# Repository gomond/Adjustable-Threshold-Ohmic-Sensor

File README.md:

# Adjustable Threshold Ohmic Sensor
 Adjustable Threshold Ohmic Sensor designed to operate with current Masso CNC Plasma
 I have added an enable override jumper so that ti will function with the current G200
 command and anticipate that, Masso in their wisdom will ad a configurable enable output pin function to
 the G200 in an upcomming release as this makes the device much safer again by allowing full gapped isolation 
 on top of the optical isolation. 
 I have also added a fuse to the design, that is up to the end user to decide on or just place a link.
 
 I have tested it on my machine and it works adequatly there is possibly a lot of room for improvement 
 and as such is public dommain so feel free to fork and alter it as you please.
 All parts for the prototype including the din mount enclosure are available from RS components.

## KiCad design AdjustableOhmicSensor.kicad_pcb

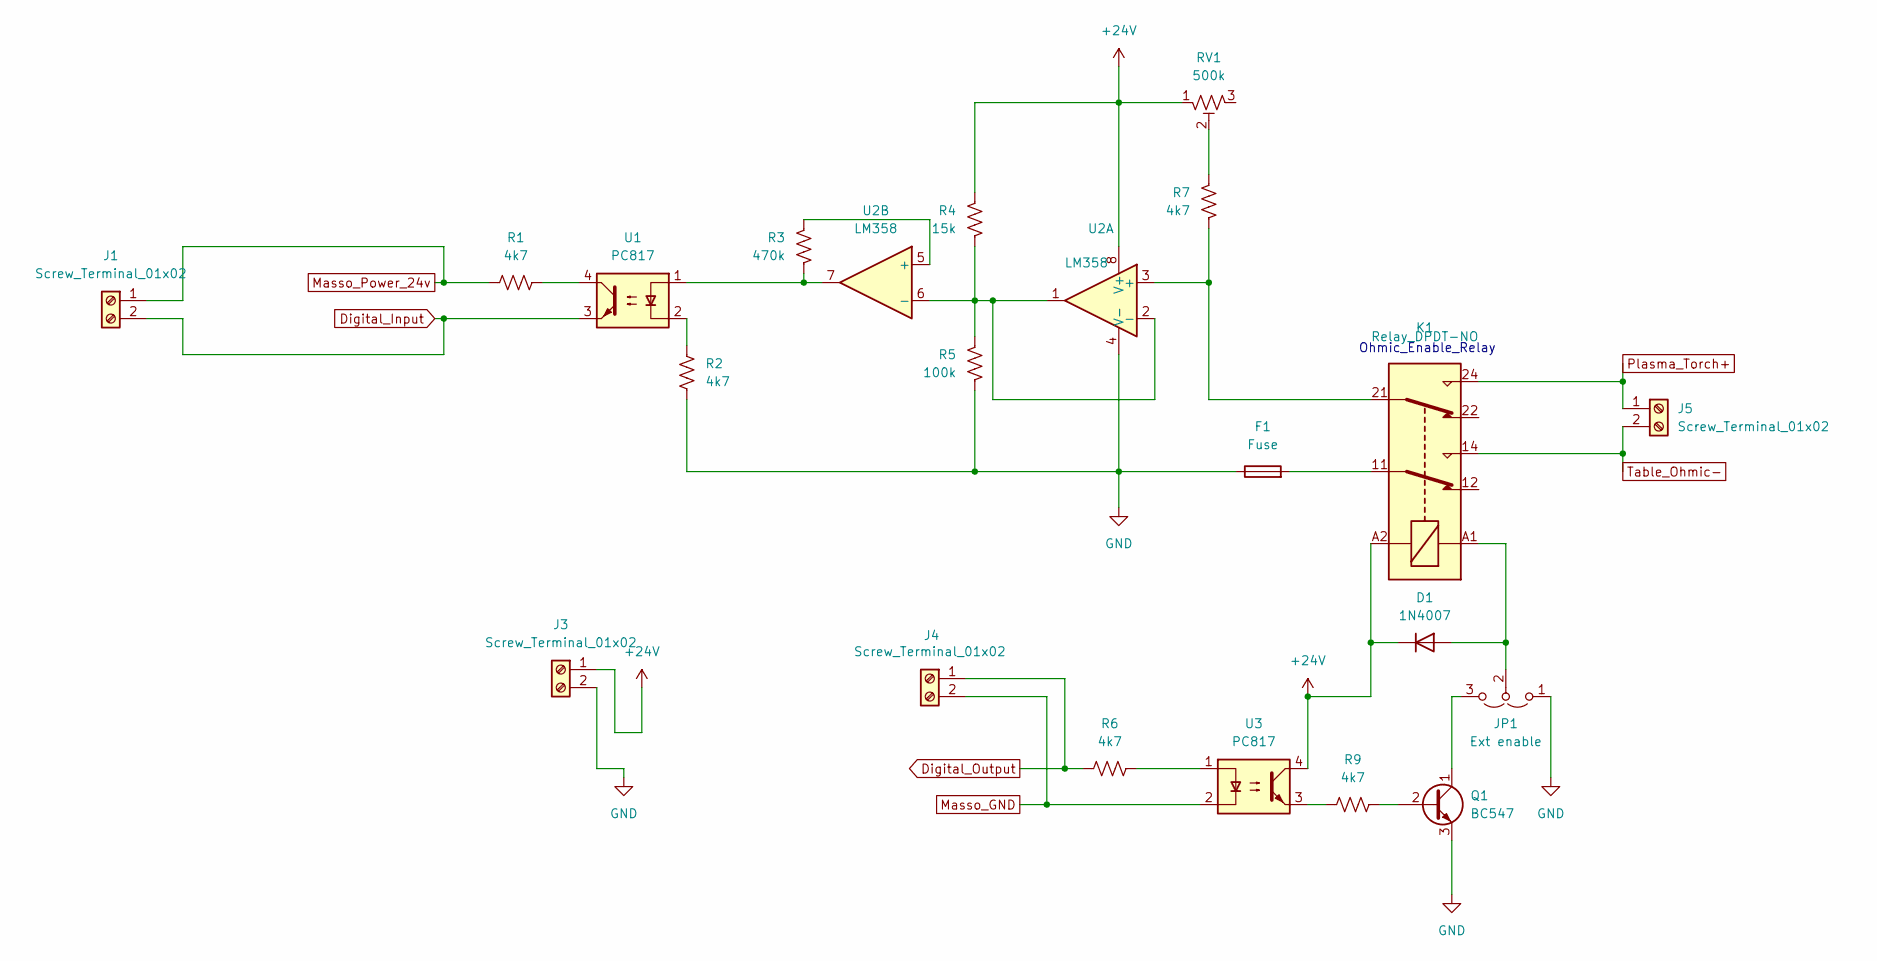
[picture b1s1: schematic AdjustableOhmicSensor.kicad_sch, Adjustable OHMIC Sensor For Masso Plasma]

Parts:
D1: 1N4007; D_DO-41_SOD81_P10.16mm_Horizontal
F1: Fuse; R_Axial_DIN0207_L6.3mm_D2.5mm_P10.16mm_Horizontal
J1, J3, J4: Screw_Terminal_01x02; TerminalBlock_bornier-2_P5.08mm
J5: Screw_Terminal_01x02; TerminalBlock_MetzConnect_Type171_RT13702HBWC_1x02_P7.50mm_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
JP1: Ext enable; PinHeader_1x03_P2.54mm_Vertical
K1: Relay_DPDT-NO; Relay_DPDT_Schrack-RT2-FormC-Dual-Coil_RM5mm
Q1: BC547; TO-92_Inline
R1, R2, R6, R7, R9: 4k7; R_Axial_DIN0207_L6.3mm_D2.5mm_P10.16mm_Horizontal
R3: 470k; R_Axial_DIN0207_L6.3mm_D2.5mm_P10.16mm_Horizontal
R4: 15k; R_Axial_DIN0207_L6.3mm_D2.5mm_P10.16mm_Horizontal
R5: 100k; R_Axial_DIN0207_L6.3mm_D2.5mm_P10.16mm_Horizontal
RV1: 500k; Potentiometer_Bourns_3296W_Vertical
U1, U3: PC817; DIP-4_W7.62mm
U2: LM358; DIP-8_W7.62mm

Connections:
+24V: D1.1 (K), J3.1, K1.A2, R4.1, RV1.1, U2.8 (V+), U3.4
Digital_Input: J1.2, U1.3
Digital_Output: J4.1, R6.1
GND: F1.1, J3.2, JP1.1 (A), Q1.3 (E), R2.1, R5.2, U2.4 (V-)
Masso_GND: J4.2, U3.2
Masso_Power_24v: J1.1, R1.1
unnamed: D1.2 (A), JP1.2 (C), K1.A1
unnamed: F1.2, K1.11
unnamed: JP1.3 (B), Q1.1 (C)
unnamed: Q1.2 (B), R9.2
unnamed: R1.2, U1.4
unnamed: R2.2, U1.2
unnamed: R3.2, U1.1, U2.7
unnamed: R6.2, U3.1
unnamed: R7.1, RV1.2
unnamed: R9.1, U3.3
unnamed: K1.21, R7.2, U2.3 (+)
unnamed: R4.2, R5.1, U2.1, U2.2 (-), U2.6 (-)
unnamed: R3.1, U2.5 (+)
Plasma_Torch+: J5.1, K1.24
Table_Ohmic-: J5.2, K1.14

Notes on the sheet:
Ohmic_Enable_Relay

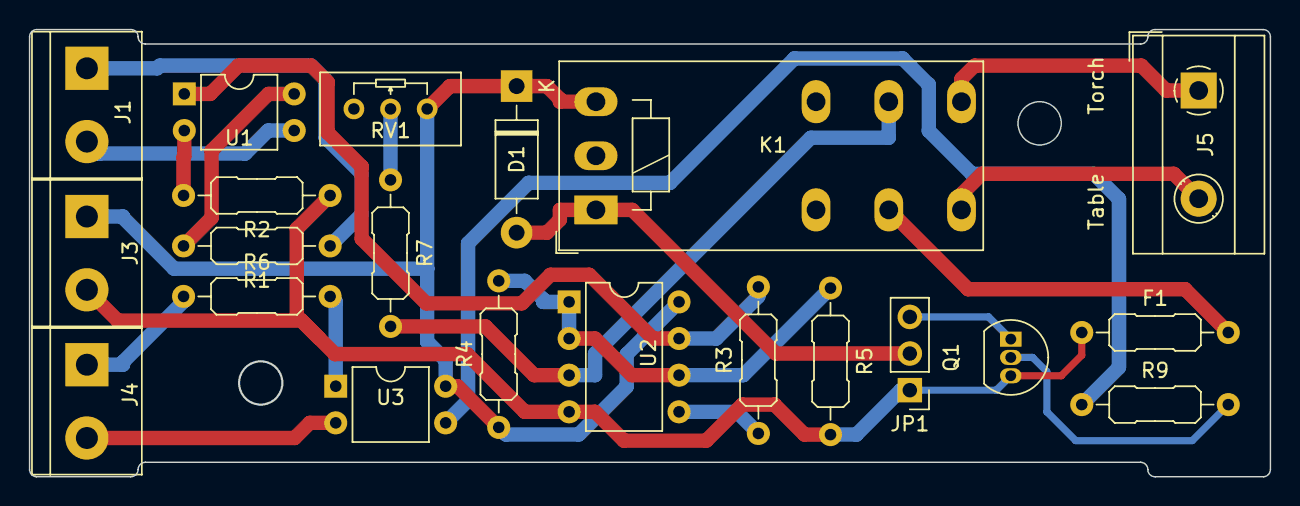
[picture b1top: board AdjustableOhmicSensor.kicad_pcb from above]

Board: 2 copper layers, 86.0 x 31.0 mm, 21 parts (0 on the bottom side), 21 nets.

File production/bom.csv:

Designator,Footprint,Quantity,Value,LCSC Part #
D1,D_DO-41_SOD81_P10.16mm_Horizontal,1,1N4007,
"J1, J3, J4, J5",TerminalBlock_bornier-2_P5.08mm,4,Screw_Terminal_01x02,
JP1,PinHeader_1x03_P2.54mm_Vertical,1,Ext enable,
K1,Relay_DPDT_Schrack-RT2-FormC-Dual-Coil_RM5mm,1,Relay_DPDT-NO,
Q1,TO-92_Inline,1,BC547,
"R1, R2, R6, R7, R9",R_Axial_DIN0309_L9.0mm_D3.2mm_P12.70mm_Horizontal,5,4k7,
R3,R_Axial_DIN0309_L9.0mm_D3.2mm_P12.70mm_Horizontal,1,470k,
R4,R_Axial_DIN0309_L9.0mm_D3.2mm_P12.70mm_Horizontal,1,15k,
R5,R_Axial_DIN0309_L9.0mm_D3.2mm_P12.70mm_Horizontal,1,100k,
R8,R_Axial_DIN0309_L9.0mm_D3.2mm_P12.70mm_Horizontal,1,20M,
RV1,Potentiometer_Bourns_3296W_Vertical,1,2M,
"U1, U3",DIP-4_W7.62mm,2,PC817,
U2,DIP-8_W7.62mm,1,LM358,

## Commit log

2024-03-24 Initial Working Commit
    Initial working commit.
    BOM and other stuff to be added soon.

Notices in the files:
AdjustableOhmicSensor.kicad_sch:
GNU General Public License
